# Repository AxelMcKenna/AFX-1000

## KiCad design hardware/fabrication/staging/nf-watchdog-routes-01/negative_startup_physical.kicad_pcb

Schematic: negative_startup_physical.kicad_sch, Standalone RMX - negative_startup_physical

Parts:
C1: 56nF50V C0G5% C1206C563J5GACTU - COMPLETE10% RECE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; PROPOSED_KEMET1206_LevelB
C2: 33nF50V C0G5% C1206C333J5GACTU - COMPLETE10% RECE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; PROPOSED_KEMET1206_LevelB
C3, C12, C39, C55, C56, C57, C58, C59, C60, C61, C62, C63, C64, C65, C66, C67, C68, C69, C70, C71, C72, C73, C74, C75, C76, C77, C78, C79, C80, C81, C82, C83, C84, C85, C86, C87, C88: 100nF 50V X7R10% C0603C104K5RACTU - bypass effect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; PROPOSED_KEMET0603_LevelB
C4, C31: 10uF 25V X7R MODULE INPUT FILTER/EFFECTIVE/INRUSH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; Capacitor_SMD__C_1206_3216Metric
C5, C32: 1uF 50V X7R MODULE OUTPUT FILTER/EFFECTIVE HOLD; Capacitor_SMD__C_1206_3216Metric
C6, C33: 1uF 25V X7R LTC4261 local VIN effective HOLD; Capacitor_SMD__C_1206_3216Metric
C7, C9, C11, C13, C34, C36, C38, C40: 100nF 25V C0G C1206C104J3GACTU; PROPOSED_KEMET1206_LevelB
C8, C10, C35, C37: 10nF 50V C0G COMPLETE10% TIMING RECEIVING; PROPOSED_KEMET1206_LevelB
C14, C15, C16, C17, C18, C19, C20, C21, C22, C23, C24, C25, C41, C42, C43, C44, C45, C46, C47, C48, C49: 100nF 50V C0G C1210C104J5GACTU - COMPLETE10% RAMP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; PROPOSED_KEMET1210_LevelB
C26, C27, C50, C51: 2.2uF 63V PET5% MKS2C042201K00JSSD - COMPLETE10% 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; Capacitor_THT__C_Rect_L7.2mm_W7.2mm_P5.00mm_FKS2_FKP2_MKS2_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
C28, C30, C52, C54: 47nF 50V C0G C1206C473J5GACTU; PROPOSED_KEMET1206_LevelB
C29, C53: 100nF 50V C0G C1210C104J5GACTU; PROPOSED_KEMET1210_LevelB
C89, C90, C91, C93, C94, C96: 100nF50V X7R10% C0603C104K5RACTU - EFFECTIVE/PDN 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; PROPOSED_KEMET0603_LevelB
C92, C95: 47nF50V C0G5% C1206C473J5GACTU - COMPLETE6% RECEI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; PROPOSED_KEMET1206_LevelB
C97, C98: 100nF25V C0G5% C1206C104J3GACTU - COMPLETE6% CT /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; PROPOSED_KEMET1206_LevelB
C99: 100nF25V C0G5% C1206C104J3GACTU - COMPLETE6% UVRE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; PROPOSED_KEMET1206_LevelB
C100: 100nF50V X7R10% C0603C104K5RACTU - LOCAL_BYPASS_E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; PROPOSED_KEMET0603_LevelB
J1: NEW NF03C CONTROL/KELVIN INTERFACE - physical con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; NC265_JST_PHD_B30B-PHDSS_2x15_P2.00mm_Vertical
J2: N19 NEW FORCE IN/OUT - connector and harness unse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; NC265_NC265_Force2_18AWG_P5_Drill2p2_Land3p8
J3: N19 E28 BANK GATE/COMMON CLAMP - physical interfa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; NC265_JST_PH_B2B-PH-K_1x02_P2.00mm_Vertical
J4: N12 NEW FORCE IN/OUT - connector and harness unse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; NC265_NC265_Force2_18AWG_P5_Drill2p2_Land3p8
J5: N12 E28 BANK GATE/COMMON CLAMP - physical interfa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; NC265_JST_PH_B2B-PH-K_1x02_P2.00mm_Vertical
J6: NEW MODULE INPUT ONLY - keyed JST XH2 receiving c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; NC265_JST_XH_B2B-XH-A_1x02_P2.50mm_Vertical
Q1, Q2: CSD19536KTT; Package_TO_SOT_SMD__TO-263-2
R1, R2, R8, R9: 10k; PROPOSED_TNPW0805_IPC28950
R3, R10: 205000ohm 0.1% TNPW0805205KBEEA - COMPLETE3% RECE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; PROPOSED_TNPW0805_IPC28950
R4, R11: 499ohm 0.1% TNPW0805499RBEEA - COMPLETE3% RECEIVI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; PROPOSED_TNPW0805_IPC28950
R5, R12, R95, R98, R99: 10000ohm 0.1% TNPW080510K0BEEA - COMPLETE3% RECEI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; PROPOSED_TNPW0805_IPC28950
R6, R7, R13, R14: 220ohm COMPLETE +/-3% RECEIVING; PROPOSED_TNPW0805_IPC28950
R15, R16, R17, R18, R19, R20, R21, R22: 47k 3% TOTAL RECEIVING; PROPOSED_TNPW0805_IPC28950
R23: 160000ohm COMPLETE0.1% RECEIVING; PROPOSED_TNPU0805_IPC28950
R24, R41, R63, R65, R80, R82: 10k COMPLETE0.1% RECEIVING; PROPOSED_TNPU0805_IPC28950
R25, R49: 8660ohm COMPLETE0.1% RECEIVING; PROPOSED_TNPU0805_IPC28950
R26, R50: 35.7ohm COMPLETE0.1% RECEIVING; PROPOSED_TNPU0603_IPC28950
R27, R31, R35, R44, R47, R51: 100k COMPLETE0.1% RECEIVING; PROPOSED_TNPU0805_IPC28950
R28, R32, R36, R37, R38, R39, R45, R48, R52, R53, R54, R55, R59, R76: 10k COMPLETE3% RECEIVING; PROPOSED_TNPW0805_IPC28950
R29, R46: 2000ohm COMPLETE0.1% RECEIVING; PROPOSED_TNPU0805_IPC28950
R30: 40.2ohm COMPLETE0.1% RECEIVING; PROPOSED_TNPU0603_IPC28950
R33: 6040ohm COMPLETE0.1% RECEIVING; PROPOSED_TNPU0805_IPC28950
R34: 75ohm COMPLETE0.1% RECEIVING; PROPOSED_TNPU0603_IPC28950
R40: 102000ohm COMPLETE0.1% RECEIVING; PROPOSED_TNPU0805_IPC28950
R42: 10700ohm COMPLETE0.1% RECEIVING; PROPOSED_TNPU0805_IPC28950
R43: 169ohm COMPLETE0.1% RECEIVING; PROPOSED_TNPU0805_IPC28950
R56, R57, R73, R74: 402ohm 1% CRCW2010402RFKEF - COMPLETE3% RECEIVING; PROPOSED_CRCW2010_reflow20035
R58, R60, R61, R66, R67, R68, R75, R77, R78, R83, R84, R85: 47k COMPLETE3% RECEIVING; PROPOSED_TNPW0805_IPC28950
R62, R79: 30.4k COMPLETE0.1% RECEIVING; PROPOSED_TNPU0805_IPC28950
R64, R81: 78.7k COMPLETE0.1% RECEIVING; PROPOSED_TNPU0805_IPC28950
R69: 0.33ohm COMPLETE5% SHUNT RECEIVING; PROPOSED_WSL2512_7m_to500m
R70, R87: 10ohm COMPLETE3% RECEIVING; PROPOSED_TNPW0805_IPC28950
R71, R88: 1M; PROPOSED_TNPW0805_IPC28950
R72: 27ohm COMPLETE3% RECEIVING; PROPOSED_TNPW0805_IPC28950
R86: 0.12ohm COMPLETE5% SHUNT RECEIVING; PROPOSED_WSL2512_7m_to500m
R89: 39ohm COMPLETE3% RECEIVING; PROPOSED_TNPW0805_IPC28950
R90, R91: 10k0.1% TNPW080510K0BEEA - COMPLETE3% RECEIVING; PROPOSED_TNPW0805_IPC28950
R92: 11300ohm 0.02% 2ppm TNPU080511K3HWEN00 - COMPLETE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; PROPOSED_TNPW0805_IPC28950
R93: 49.9ohm 0.1% TNPW080549R9BEEA - COMPLETE0.7% TRIM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; PROPOSED_TNPW0805_IPC28950
R94: 10000ohm 0.02% 2ppm TNPU080510K0HWEN00 - COMPLETE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; PROPOSED_TNPW0805_IPC28950
R96: 47000ohm 0.1% TNPW080547K0BEEA - COMPLETE3% RECEI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; PROPOSED_TNPW0805_IPC28950
R97: 680ohm 0.1% TNPW1206680RBEEA - COMPLETE3% RECEIVI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; PROPOSED_TNPW1206_IPC28950
U1, U2, U7, U8: SN74AUP1G74DCUR; NF05R_Manufacturer__TI_DCU0008A
U3, U9: TPS3431SDRBR; TI_DRB0008A_TPS3431
U4, U10: SN74LVC1G06DBVR; Package_TO_SOT_SMD__SOT-23-5
U5, U6, U11, U12: TLP4590AF(F; Package_DIP__DIP-6_W10.16mm
U13: OPA2333AID; Package_SO__SOIC-8_3.9x4.9mm_P1.27mm
U14: TLV1822DR; Package_SO__SOIC-8_3.9x4.9mm_P1.27mm
U15: TLV1824DR; Package_SO__SOIC-14_3.9x8.7mm_P1.27mm
U16, U27: SN74LVC2T45DCUR; NF05R_Manufacturer__TI_DCU0008A
U17, U22: TMR 1-1215; Converter_DCDC__Converter_DCDC_TRACO_TMR-1-xxxx_Single_THT
U18, U23: LTC4261IGN#PBF; Package_SO__SSOP-28_3.9x9.9mm_P0.635mm
U19, U24: ISO7721FDR; Package_SO__SOIC-8_3.9x4.9mm_P1.27mm
U20, U21, U25, U26, U52, U54, U56: TPS389001DSET; Package_SON__WSON-6_1.5x1.5mm_P0.5mm
U28, U30, U53, U55: SN74LVC1G17DCKR; NF05R_Manufacturer__TI_DCK0005A
U29, U31, U32, U33, U34, U49: SN74AUP2G14DCKR; NF05R_Manufacturer__TI_DCK0006A
U35, U36, U37, U38, U39, U40, U41, U42, U43, U44, U51: SN74HCS08PWR; Package_SO__TSSOP-14_4.4x5mm_P0.65mm
U45, U46: SN74HCS32PWR; Package_SO__TSSOP-14_4.4x5mm_P0.65mm
U47, U48: SN74HCS14PWR; Package_SO__TSSOP-14_4.4x5mm_P0.65mm
U50: SN74HCS02PWR; Package_SO__TSSOP-14_4.4x5mm_P0.65mm
U57: TPS22919DCKR; NF05R_Manufacturer__TI_DCK0006A
U58: SN74LVC1G14DCKR; NF05R_Manufacturer__TI_DCK0005A

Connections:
/ABS_AUX_CT: C99.1, U56.5 (CT)
/ABS_AUX_FAULT: J1.7 (ABS_AUX_FAULT_MONITOR_OUTPUT_ONLY), R17.1, U48.13 (6A), U58.4 (Y)
/ABS_AUX_READY: U48.12 (6Y), U51.13 (4B)
/ABS_AUX_SENSE: R93.2, R94.1, U56.1 (SENSE)
/ABS_AUX_TOP_TRIM: R92.2, R93.1
/AGND: C1.2, C2.2, C3.2, C12.2, C39.2, C55.2, C56.2, C57.2, C58.2, C59.2, C60.2, C61.2, C62.2, C63.2, C64.2, C65.2, C66.2, C67.2, C68.2, C69.2, C70.2, C71.2, C72.2, C73.2, C74.2, C75.2, C76.2, C77.2, C78.2, C79.2, C80.2, C81.2, C82.2, C83.2, C84.2, C85.2, C86.2, C87.2, C88.2, C89.2, C90.2, C91.2, C92.2, C93.2, C94.2, C95.2, C96.2, C97.2, C98.2, C99.2, C100.2, J1.2 (AGND), R3.2, R10.2, R15.2, R16.2, R17.2, R18.2, R19.2, R20.2, R21.2, R22.2, R27.2, R31.2, R35.2, R44.2, R47.2, R51.2, R59.2, R61.2, R67.2, R68.2, R76.2, R78.2, R84.2, R85.2, R94.2, R96.2, R97.2, U1.4 (GND), U2.4 (GND), U3.4 (GND), U3.9 (EP), U4.3 (GND), U7.4 (GND), U8.4 (GND), U9.4 (GND), U9.9 (EP), U10.3 (GND), U13.3 (INA+), U13.4 (V-), U13.5 (INB+), U14.4 (V-), U15.12 (V-), U16.4 (GND), U19.5 (GND2), U24.5 (GND2), U27.4 (GND), U28.3 (GND), U29.2 (GND), U30.3 (GND), U31.2 (GND), U32.2 (GND), U33.2 (GND), U34.2 (GND), U35.7 (GND), U36.7 (GND), U37.7 (GND), U38.7 (GND), U39.7 (GND), U40.7 (GND), U41.7 (GND), U42.7 (GND), U43.7 (GND), U44.7 (GND), U45.7 (GND), U46.7 (GND), U46.12 (4A), U46.13 (4B), U47.7 (GND), U48.7 (GND), U49.2 (GND), U50.7 (GND), U51.7 (GND), U52.2 (GND), U53.3 (GND), U54.2 (GND), U55.3 (GND), U56.2 (GND), U57.2 (GND), U58.3 (GND)
/AUX2V6: C3.1, C12.1, C56.1, C57.1, C58.1, C59.1, C60.1, C61.1, C62.1, C63.1, C64.1, C65.1, C66.1, C67.1, C68.1, C69.1, C70.1, C71.1, C72.1, C73.1, C74.1, C75.1, C76.1, C77.1, C78.1, C79.1, C80.1, C81.1, C82.1, C83.1, C84.1, C85.1, C86.1, C87.1, C88.1, C89.1, C90.1, C91.1, C93.1, C94.1, C96.1, C100.1, J1.1 (AUX2V6), R1.1, R2.1, R8.1, R9.1, R37.1, R38.1, R39.1, R53.1, R54.1, R55.1, R90.1, R91.1, R92.1, U1.7 (PRE_N), U1.8 (VCC), U2.2 (D), U2.7 (PRE_N), U2.8 (VCC), U3.1 (VDD), U4.5 (VCC), U7.7 (PRE_N), U7.8 (VCC), U8.2 (D), U8.7 (PRE_N), U8.8 (VCC), U9.1 (VDD), U10.5 (VCC), U13.8 (V+), U14.8 (V+), U15.3 (V+), U16.1 (VCCA), U16.5 (DIR), U27.8 (VCCB), U28.5 (VCC), U29.5 (VCC), U30.5 (VCC), U31.5 (VCC), U32.5 (VCC), U33.5 (VCC), U34.5 (VCC), U35.14 (VCC), U36.14 (VCC), U37.14 (VCC), U38.14 (VCC), U39.14 (VCC), U40.14 (VCC), U41.14 (VCC), U42.14 (VCC), U43.14 (VCC), U44.14 (VCC), U45.14 (VCC), U46.14 (VCC), U47.14 (VCC), U48.14 (VCC), U49.5 (VCC), U50.14 (VCC), U51.14 (VCC), U52.3 (MR), U52.4 (VDD), U53.5 (VCC), U54.3 (MR), U54.4 (VDD), U55.5 (VCC), U58.5 (VCC)
/AUX_VALID: J1.5 (AUX_VALID), R16.1, U35.1 (1A)
/CLAMP_LED_SUPPLY: C98.1, R4.1, R11.1, R97.1, U57.6 (VOUT)
/CLAMP_SUPPLY_ENABLE: R95.2, R96.1, U56.6 (RESET_N), U57.3 (ON), U58.2 (A)
/DIG5_FORCE: C39.1, C55.1, C97.1, J1.3 (DIG5_FORCE), R95.1, U16.8 (VCCB), U19.8 (VCC2), U24.8 (VCC2), U27.1 (VCCA), U27.5 (DIR), U56.3 (MR), U56.4 (VDD), U57.1 (IN)
/E28_COMBINED_FAULT_REQUEST: J1.14 (E28_COMBINED_FAULT_REQUEST), U34.4 (2Y)
/E28_COMBINED_FAULT_REQUEST_BUFFER_MID: U34.3 (2A), U34.6 (1Y)
/E28_COMBINED_FAULT_REQUEST_HCS: U34.1 (1A), U46.6 (2Y)
/E28_NATIVE_FAULT_REQUEST: J1.13 (E28_NATIVE_FAULT_REQUEST), U46.4 (2A)
/E28_NOT_FAULT: J1.15 (E28_NOT_FAULT), R22.1, U44.4 (2A)
/GLOBAL_MASTER: J1.6 (GLOBAL_MASTER), R15.1, U35.2 (1B)
/GLOBAL_VALID: U35.3 (1Y), U35.4 (2A), U35.5 (2B), U35.12 (4A), U37.4 (2A), U38.5 (2B), U38.13 (4B), U40.12 (4A), U41.13 (4B), U48.11 (5A), U51.1 (1A), U51.4 (2A)
/GUARDED_12V_FORCE: C4.1, C31.1, J6.1 (GUARDED12), U17.2 (+VIN), U22.2 (+VIN)
/MODULE_INPUT_GND: C4.2, C31.2, J6.2 (MODULE_RETURN), U17.1 (-VIN), U22.1 (-VIN)
/N12_ARM_CONDITIONED: J1.24 (N12_ARM_MONITOR_OUTPUT_ONLY), R20.1, U30.4 (Y), U39.1 (1A), U40.13 (4B), U41.12 (4A), U54.1 (SENSE)
/N12_ARM_Q: U30.2 (A), U50.10 (3Y), U50.12 (4B)
/N12_ARM_QBAR: U50.9 (3B), U50.13 (4Y)
/N12_ARM_SET: U50.11 (4A), U51.8 (3Y)
/N12_BANK_CLAMP_GATE: R14.2, U12.4 (D1)
/N12_BANK_COMMON: J5.2 (BANK_COMMON), U12.6 (D2)
/N12_BANK_GATE: J5.1 (BANK_GATE), R14.1
/N12_BIAS_CT: C37.1, U25.5 (CT)
/N12_BIAS_HOST5: R84.1, U24.6 (OUTB), U27.3 (A2)
/N12_BIAS_RESET_N: R83.2, U24.3 (INB), U25.6 (RESET_N), U26.6 (RESET_N)
/N12_BIAS_SENSE: R79.2, R80.1, U25.1 (SENSE)
/N12_BIAS_VALID: J1.17 (N12_BIAS_VALID), R85.1, U27.6 (B2), U43.13 (4B)
/N12_CG_SERIES: C52.1, R87.2
/N12_CLAMPS_RELEASE: J1.28 (N12_CLAMPS_RELEASE), R10.1, U10.2 (A), U33.4 (2Y)
/N12_CLAMPS_RELEASE_BUFFER_MID: U33.3 (2A), U33.6 (1Y)
/N12_CLAMPS_RELEASE_HCS: U33.1 (1A), U42.3 (1Y)
/N12_CLAMP_LED_A: R11.2, R12.1, U11.1 (LED_A)
/N12_CLAMP_LED_K: R99.2, U10.4 (Y), U12.2 (LED_K)
/N12_CLAMP_LED_MID: R12.2, R99.1, U11.2 (LED_K), U12.1 (LED_A)
/N12_COMPLETE: J1.27 (N12_COMPLETE), U8.5 (Q), U39.12 (4A), U44.12 (4A)
/N12_COMPLETE_CLK: U8.1 (CLK), U41.8 (3Y)
/N12_COMPLETE_CLR_N: U8.6 (CLR_N), U41.11 (4Y)
/N12_CONTROLLER_ON: R77.1, U23.2 (ON), U24.2 (OUTA)
/N12_CR_TOP: C41.1, C42.1, C43.1, C44.1, C45.1, C46.1, C47.1, C48.1, C49.1, R89.2
/N12_CWD: C2.1, U9.2 (CWD)
/N12_DRAIN_SENSE: R88.2, U23.16 (DRAIN)
/N12_E28_SRC: C41.2, C42.2, C43.2, C44.2, C45.2, C46.2, C47.2, C48.2, C49.2, J4.2 (E28_SRC), Q2.2 (D), R88.1
/N12_F0: U45.8 (3Y), U45.12 (4A)
/N12_FAULT_REQUEST: J1.26 (N12_FAULT_REQUEST), U45.11 (4Y), U46.2 (1B)
/N12_FEED_MID: R73.2, R74.1
/N12_F_OUTPUT: U39.11 (4Y), U45.13 (4B)
/N12_F_SOURCE: U39.3 (1Y), U45.9 (3A)
/N12_F_TIMEOUT: U39.8 (3Y), U45.10 (3B)
/N12_F_WD_ARM: U39.6 (2Y), U39.9 (3A)
/N12_INTVCC: C34.1, C36.1, C38.1, C40.1, R79.1, R83.1, U23.5 (SDAI), U23.6 (SCL), U23.7 (INTVCC), U23.8 (UVL), U23.9 (UVH), U23.22 (FLTIN), U24.1 (VCC1), U25.3 (MR_N), U25.4 (VDD), U26.3 (MR_N), U26.4 (VDD)
/N12_ISO24: C32.1, R73.1, U22.4 (+VOUT)
/N12_NOT_COMPLETE: U8.3 (NOT_Q), U9.5 (SET1)
/N12_NOT_PERMIT: U7.3 (NOT_Q), U9.6 (WDI)
/N12_NOT_READY: U39.13 (4B), U47.10 (5Y)
/N12_NOT_SAFE: U39.2 (1B), U47.8 (4Y)
/N12_NOT_WDO: U39.10 (3B), U47.12 (6Y)
/N12_OUTPUT_OV_GOOD: R55.2, U15.13 (OUT4), U43.10 (3B), U44.2 (1B)
/N12_OUTPUT_QUALIFIED: U44.11 (4Y), U48.5 (3A)
/N12_OUTPUT_UV_GOOD: R54.2, U15.14 (OUT3), U44.1 (1A)
/N12_OUT_INV: R41.1, R45.1, R48.1, U13.7 (OUTB)
/N12_OUT_OV_REF: R46.2, R47.1, U15.11 (IN4+)
/N12_OUT_OV_SENSE: R48.2, U15.10 (IN4-)
/N12_OUT_SUM: R40.2, R41.2, U13.6 (INB-)
/N12_OUT_UV_REF: R43.2, R44.1, U15.8 (IN3-)
/N12_OUT_UV_RMID: R42.2, R43.1
/N12_OUT_UV_SENSE: R45.2, U15.9 (IN3+)
/N12_OV_OK: J1.10 (N12_OV_OK), U43.5 (2B)
/N12_OV_SENSE: J1.12 (N12_OV_SENSE), R52.1
/N12_P03_SRC: C32.2, C33.2, C34.2, C35.2, C36.2, C37.2, C38.2, C40.2, C50.2, C51.2, C52.2, C53.2, C54.2, J4.1 (P03_SRC), R75.2, R76.1, R77.2, R80.2, R82.2, R86.1, U22.6 (-VOUT), U23.1 (PGI), U23.3 (ALERT), U23.10 (ADIN2), U23.11 (OV), U23.13 (VEE), U23.23 (ADIN), U23.24 (ADR0), U23.25 (ADR1), U23.26 (EN), U23.27 (PG), U24.4 (GND1), U25.2 (GND), U26.2 (GND)
/N12_PASS_CLAMP_GATE: R13.2, U11.4 (D1)
/N12_PASS_GATE: Q2.1 (G), R13.1, R87.1, U23.15 (GATE)
/N12_PASS_SOURCE: Q2.3 (S), R86.2, U11.6 (D2), U23.14 (SENSE)
/N12_PCLR0: U40.11 (4Y), U41.1 (1A), U42.1 (1A)
/N12_PCLR1: U41.3 (1Y), U41.4 (2A)
/N12_PERMIT: U7.5 (Q), U16.3 (A2), U41.9 (3A)
/N12_PERMIT_CLR_N: U7.6 (CLR_N), U41.6 (2Y)
/N12_PERMIT_D: U7.2 (D), U40.8 (3Y), U51.10 (3B)
/N12_PROTECTED: J1.29 (N12_PROTECTED), R40.1
/N12_RAMP: C50.1, C51.1, R89.1, U23.18 (RAMP)
/N12_READY: U41.10 (3B), U44.3 (1Y), U44.13 (4B), U47.11 (5A)
/N12_RUN_HOST5: R78.1, U16.6 (B2), U24.7 (INA)
/N12_SAFE: U40.5 (2B), U41.5 (2B), U43.11 (4Y), U47.9 (4A)
/N12_SOURCE_SAFE0: U43.6 (2Y), U43.9 (3A)
/N12_SOURCE_SAFE1: U43.8 (3Y), U43.12 (4A)
/N12_SOURCE_UV_GOOD: R53.2, U14.7 (OUT2), U43.4 (2A)
/N12_SOURCE_UV_REF: R50.2, R51.1, U14.6 (IN2-)
/N12_SOURCE_UV_RMID: R49.2, R50.1
/N12_SOURCE_UV_SENSE: R52.2, U14.5 (IN2+)
/N12_SS: C53.1, U23.19 (SS)
/N12_STAGE_ENABLED: U38.12 (4A), U39.4 (2A), U51.6 (2Y), U51.9 (3A)
/N12_START: J1.25 (N12_START_MONITOR_OUTPUT_ONLY), R21.1, U31.1 (1A), U55.4 (Y)
/N12_START_ARMED: U40.3 (1Y), U40.4 (2A)
/N12_START_CONDITIONED: U7.1 (CLK), U31.4 (2Y)
/N12_START_CONDITIONED_BUFFER_MID: U31.3 (2A), U31.6 (1Y)
/N12_START_CT: C95.1, U54.5 (CT)
/N12_START_DELAY_N: R91.2, U54.6 (RESET_N), U55.2 (A)
/N12_START_SAFE: U40.6 (2Y), U40.9 (3A)
/N12_TMR: C54.1, U23.20 (TMR)
/N12_VIN: C33.1, R74.2, R75.1, R81.1, U23.21 (VIN)
/N12_VIN_VALID_CT: C35.1, U26.5 (CT)
/N12_VIN_VALID_SENSE: R81.2, R82.1, U26.1 (SENSE)
/N12_WDO: R8.2, U9.7 (WDO), U40.2 (1B), U47.13 (6A)
/N12_WD_ARMED: R9.2, U9.8 (ENOUT), U39.5 (2B), U40.1 (1A)
/N12_WD_ENABLE: U9.3 (EN), U38.11 (4Y)
/N19_ARM_CONDITIONED: J1.18 (N19_ARM_MONITOR_OUTPUT_ONLY), R18.1, U28.4 (Y), U35.9 (3A), U37.5 (2B), U38.4 (2A), U52.1 (SENSE)
/N19_ARM_Q: U28.2 (A), U50.1 (1Y), U50.6 (2B)
/N19_ARM_QBAR: U50.3 (1B), U50.4 (2Y)
/N19_ARM_SET: U50.5 (2A), U51.3 (1Y)
/N19_BANK_CLAMP_GATE: R7.2, U6.4 (D1)
/N19_BANK_COMMON: J3.2 (BANK_COMMON), U6.6 (D2)
/N19_BANK_GATE: J3.1 (BANK_GATE), R7.1
/N19_BIAS_CT: C10.1, U20.5 (CT)
/N19_BIAS_HOST5: R67.1, U19.6 (OUTB), U27.2 (A1)
/N19_BIAS_RESET_N: R66.2, U19.3 (INB), U20.6 (RESET_N), U21.6 (RESET_N)
/N19_BIAS_SENSE: R62.2, R63.1, U20.1 (SENSE)
/N19_BIAS_VALID: J1.16 (N19_BIAS_VALID), R68.1, U27.7 (B1), U42.13 (4B)
/N19_CG_SERIES: C28.1, R70.2
/N19_CLAMPS_RELEASE: J1.22 (N19_CLAMPS_RELEASE), R3.1, U4.2 (A), U32.4 (2Y)
/N19_CLAMPS_RELEASE_BUFFER_MID: U32.3 (2A), U32.6 (1Y)
/N19_CLAMPS_RELEASE_HCS: U32.1 (1A), U38.8 (3Y)
/N19_CLAMP_LED_A: R4.2, R5.1, U5.1 (LED_A)
/N19_CLAMP_LED_K: R98.2, U4.4 (Y), U6.2 (LED_K)
/N19_CLAMP_LED_MID: R5.2, R98.1, U5.2 (LED_K), U6.1 (LED_A)
/N19_COMPLETE: J1.21 (N19_COMPLETE), U2.5 (Q), U36.4 (2A), U44.9 (3A)
/N19_COMPLETE_CLK: U2.1 (CLK), U38.3 (1Y)
/N19_COMPLETE_CLR_N: U2.6 (CLR_N), U38.6 (2Y)
/N19_CONTROLLER_ON: R60.1, U18.2 (ON), U19.2 (OUTA)
/N19_CR_TOP: C14.1, C15.1, C16.1, C17.1, C18.1, C19.1, C20.1, C21.1, C22.1, C23.1, C24.1, C25.1, R72.2
/N19_CWD: C1.1, U3.2 (CWD)
/N19_DRAIN_SENSE: R71.2, U18.16 (DRAIN)
/N19_E28_SRC: C14.2, C15.2, C16.2, C17.2, C18.2, C19.2, C20.2, C21.2, C22.2, C23.2, C24.2, C25.2, J2.2 (E28_SRC), Q1.2 (D), R71.1
/N19_F0: U45.3 (1Y), U45.4 (2A)
/N19_FAULT_REQUEST: J1.20 (N19_FAULT_REQUEST), U45.6 (2Y), U46.1 (1A)
/N19_FEED_MID: R56.2, R57.1
/N19_F_OUTPUT: U36.6 (2Y), U45.5 (2B)
/N19_F_SOURCE: U35.8 (3Y), U45.1 (1A)
/N19_F_TIMEOUT: U36.3 (1Y), U45.2 (1B)
/N19_F_WD_ARM: U35.11 (4Y), U36.1 (1A)
/N19_INTVCC: C7.1, C9.1, C11.1, C13.1, R62.1, R66.1, U18.5 (SDAI), U18.6 (SCL), U18.7 (INTVCC), U18.8 (UVL), U18.9 (UVH), U18.22 (FLTIN), U19.1 (VCC1), U20.3 (MR_N), U20.4 (VDD), U21.3 (MR_N), U21.4 (VDD)
/N19_ISO24: C5.1, R56.1, U17.4 (+VOUT)
/N19_NOT_COMPLETE: U2.3 (NOT_Q), U3.5 (SET1)
/N19_NOT_PERMIT: U1.3 (NOT_Q), U3.6 (WDI)
/N19_NOT_READY: U36.5 (2B), U47.4 (2Y)
/N19_NOT_SAFE: U35.10 (3B), U47.2 (1Y)
/N19_NOT_WDO: U36.2 (1B), U47.6 (3Y)
/N19_OUTPUT_OV_GOOD: R39.2, U15.1 (OUT2), U42.10 (3B), U43.2 (1B)
/N19_OUTPUT_QUALIFIED: U44.8 (3Y), U48.3 (2A), U51.5 (2B)
/N19_OUTPUT_UV_GOOD: R38.2, U15.2 (OUT1), U43.1 (1A)
/N19_OUT_INV: R24.1, R28.1, R32.1, U13.1 (OUTA)
/N19_OUT_OV_REF: R30.2, R31.1, U15.7 (IN2+)
/N19_OUT_OV_RMID: R29.2, R30.1
/N19_OUT_OV_SENSE: R32.2, U15.6 (IN2-)
/N19_OUT_SUM: R23.2, R24.2, U13.2 (INA-)
/N19_OUT_UV_REF: R26.2, R27.1, U15.4 (IN1-)
/N19_OUT_UV_RMID: R25.2, R26.1
/N19_OUT_UV_SENSE: R28.2, U15.5 (IN1+)
/N19_OV_OK: J1.9 (N19_OV_OK), U42.5 (2B)
/N19_OV_SENSE: J1.11 (N19_OV_SENSE), R36.1
/N19_P03_SRC: C5.2, C6.2, C7.2, C8.2, C9.2, C10.2, C11.2, C13.2, C26.2, C27.2, C28.2, C29.2, C30.2, J2.1 (P03_SRC), R58.2, R59.1, R60.2, R63.2, R65.2, R69.1, U17.6 (-VOUT), U18.1 (PGI), U18.3 (ALERT), U18.10 (ADIN2), U18.11 (OV), U18.13 (VEE), U18.23 (ADIN), U18.24 (ADR0), U18.25 (ADR1), U18.26 (EN), U18.27 (PG), U19.4 (GND1), U20.2 (GND), U21.2 (GND)
/N19_PASS_CLAMP_GATE: R6.2, U5.4 (D1)
/N19_PASS_GATE: Q1.1 (G), R6.1, R70.1, U18.15 (GATE)
/N19_PASS_SOURCE: Q1.3 (S), R69.2, U5.6 (D2), U18.14 (SENSE)
/N19_PCLR0: U37.6 (2Y), U37.9 (3A), U38.9 (3A)
/N19_PCLR1: U37.8 (3Y), U37.12 (4A)
/N19_PERMIT: U1.5 (Q), U16.2 (A1), U38.1 (1A)
/N19_PERMIT_CLR_N: U1.6 (CLR_N), U37.11 (4Y)
/N19_PERMIT_D: U1.2 (D), U37.3 (1Y), U51.2 (1B)
/N19_PROTECTED: J1.23 (N19_PROTECTED), R23.1
/N19_RAMP: C26.1, C27.1, R72.1, U18.18 (RAMP)
/N19_READY: U38.2 (1B), U43.3 (1Y), U44.10 (3B), U47.3 (2A)
/N19_RUN_HOST5: R61.1, U16.7 (B1), U19.7 (INA)
/N19_SAFE: U36.13 (4B), U37.13 (4B), U47.1 (1A), U51.11 (4Y)
/N19_SAFE_SOURCE: U42.11 (4Y), U51.12 (4A)
/N19_SOURCE_SAFE0: U42.6 (2Y), U42.9 (3A)
/N19_SOURCE_SAFE1: U42.8 (3Y), U42.12 (4A)
/N19_SOURCE_UV_GOOD: R37.2, U14.1 (OUT1), U42.4 (2A)
/N19_SOURCE_UV_REF: R34.2, R35.1, U14.2 (IN1-)
/N19_SOURCE_UV_RMID: R33.2, R34.1
/N19_SOURCE_UV_SENSE: R36.2, U14.3 (IN1+)
/N19_SS: C29.1, U18.19 (SS)
/N19_START: J1.19 (N19_START_MONITOR_OUTPUT_ONLY), R19.1, U29.1 (1A), U53.4 (Y)
/N19_START_ARMED: U36.8 (3Y), U36.12 (4A)
/N19_START_CONDITIONED: U1.1 (CLK), U29.4 (2Y)
/N19_START_CONDITIONED_BUFFER_MID: U29.3 (2A), U29.6 (1Y)
/N19_START_CT: C92.1, U52.5 (CT)
/N19_START_DELAY_N: R90.2, U52.6 (RESET_N), U53.2 (A)
/N19_START_SAFE: U36.11 (4Y), U37.1 (1A)
/N19_TMR: C30.1, U18.20 (TMR)
/N19_VIN: C6.1, R57.2, R58.1, R64.1, U18.21 (VIN)
/N19_VIN_VALID_CT: C8.1, U21.5 (CT)
/N19_VIN_VALID_SENSE: R64.2, R65.1, U21.1 (SENSE)
/N19_WDO: R1.2, U3.7 (WDO), U36.10 (3B), U47.5 (3A)
/N19_WD_ARMED: R2.2, U3.8 (ENOUT), U35.13 (4B), U36.9 (3A)
/N19_WD_ENABLE: U3.3 (EN), U35.6 (2Y)
/NF_FAULT_REQUEST: U46.3 (1Y), U46.5 (2B), U48.1 (1A)
/NF_NOT_OUTPUT_VALID: U46.8 (3Y), U48.9 (4A)
/NF_NO_FAULT: U37.2 (1B), U37.10 (3B), U38.10 (3B), U40.10 (3B), U41.2 (1B), U42.2 (1B), U44.6 (2Y)
/NF_OUTPUT_VALID: J1.30 (NF_OUTPUT_VALID), U49.4 (2Y)
/NF_OUTPUT_VALID_BUFFER_MID: U49.3 (2A), U49.6 (1Y)
/NF_OUTPUT_VALID_HCS: U48.8 (4Y), U49.1 (1A)
/NOT_GLOBAL_VALID: U48.10 (5Y), U50.2 (1A), U50.8 (3A)
/NOT_N12_OUTPUT_QUALIFIED: U46.10 (3B), U48.6 (3Y)
/NOT_N19_OUTPUT_QUALIFIED: U46.9 (3A), U48.4 (2Y)
/NOT_NF_FAULT_REQUEST: U44.5 (2B), U48.2 (1Y)
/PROTECT_REF: J1.8 (PROTECT_REF), R25.1, R29.1, R33.1, R42.1, R46.1, R49.1

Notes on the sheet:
NF06P: captured265-part NF05R circuit with explicit physical-land/connector proposals.
Actual primitive/MPN heights, complete tolerances, routing, return coupling and installed assembly require fresh review.
Prototype only; physical/partial-power/faultenergy/fabrication acceptance FALSE.

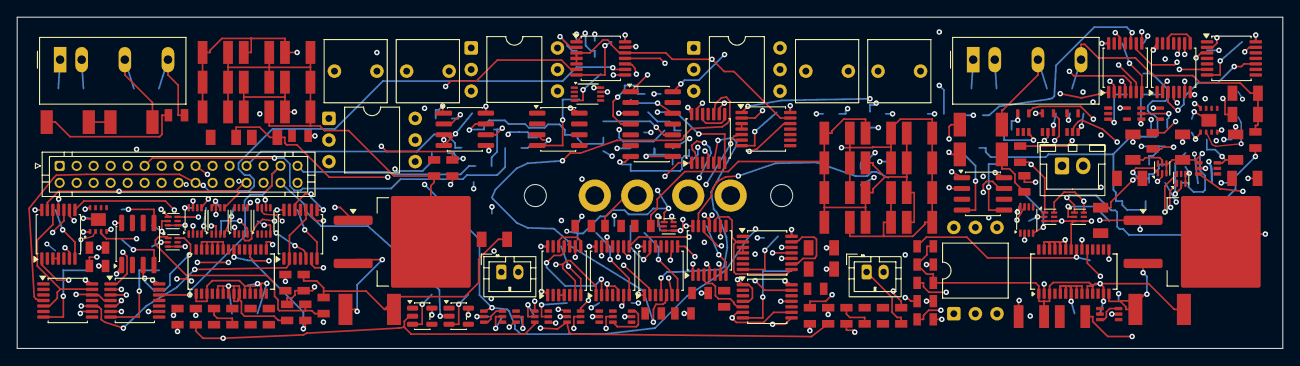
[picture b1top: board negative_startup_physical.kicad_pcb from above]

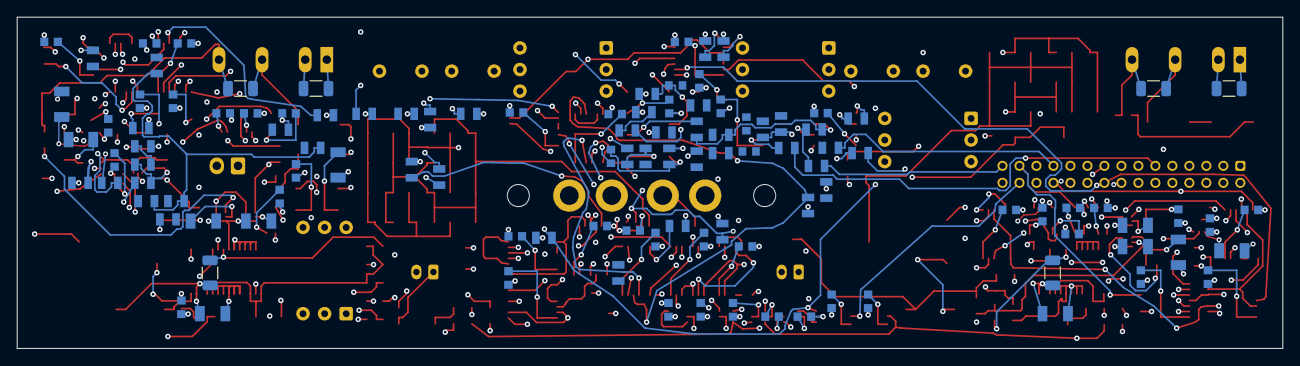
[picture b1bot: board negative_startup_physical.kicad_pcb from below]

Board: 6 copper layers, 149.0 x 39.0 mm, 267 parts (113 on the bottom side), 210 nets.

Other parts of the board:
H101, H102: STRAIN_POST_2p6_NPTH_RECEIVING

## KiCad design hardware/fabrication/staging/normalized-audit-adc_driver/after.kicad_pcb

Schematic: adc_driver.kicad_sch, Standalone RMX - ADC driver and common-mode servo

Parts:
C1, C2, C15, C16: 1pF C0G +/-0.1pF; C_0402_1005Metric
C3, C17: 47pF C0G 5%; C_0805_2012Metric
C4, C5, C18, C19: 22pF C0G 5%; C_0805_2012Metric
C6, C20: 100nF 25V X7R; C_0805_2012Metric
C7, C21: 1uF 63V film 10%; C_Rect_L7.2mm_W5.0mm_P5.00mm
C8, C22: 10uF 16V X7R; C_1206_3216Metric
C9, C23: 47uF 25V X7S; C_1210_3225Metric
C10, C11, C24, C25: 47uF 6.3V X7S; C_1206_3216Metric
C12, C26: 2.2uF 16V X7R; C_0805_2012Metric
C13, C14, C27, C28: 100nF 16V X7R; C_0402_1005Metric
C29, C30, C31, C32: 100nF 50V X7R; C_0805_2012Metric
C33, C34: 10uF 50V X7R; C_1206_3216Metric
C35, C36: 100nF 16V X7R; C_0603_1608Metric
D1, D2: BAT54S,215; SOT-23
J1: Conn_01x03; PinHeader_1x03_P2.54mm_Vertical
J2: Conn_02x10_Odd_Even; PinHeader_2x10_P2.54mm_Vertical
J3, J4: Conn_01x04; PinHeader_1x04_P2.54mm_Vertical
R1, R2, R17, R18: 2.49k 0.05%; R_0402_1005Metric
R3, R4, R19, R20: 1.21k 0.05%; R_0402_1005Metric
R5, R6, R21, R22: 3.3R 1%; R_0805_2012Metric
R7, R23: 1M 1%; R_0805_2012Metric
R8, R9, R24, R25: 100k 0.01%; R_0805_2012Metric
R10, R11, R26, R27: 10k 0.1%; R_0805_2012Metric
R12, R28: 10M 1%; R_0805_2012Metric
R13, R29: 10k 1%; R_0805_2012Metric
R14, R30: 47k 1%; R_0805_2012Metric
R15, R31: 68k 1%; R_0805_2012Metric
R16, R32: 0.1R 1%; R_0805_2012Metric
R33: 1k 1%; R_0805_2012Metric
R34, R36: 100k 0.01%; R_0603_1608Metric
R35, R37, R39, R41: 10k 0.01%; R_0603_1608Metric
R38: 161k 0.01%; R_0805_2012Metric
R40: 240k 0.01%; R_0805_2012Metric
R42, R43: 10k 1%; R_0603_1608Metric
R44: 100k 1%; R_0603_1608Metric
U1, U2: THS4551IDGKR; VSSOP-8_3x3mm_P0.65mm
U3: OPA1656ID; SOIC-8_3.9x4.9mm_P1.27mm
U4: OPA4192ID; SOIC-14_3.9x8.7mm_P1.27mm
U5, U6: LM7705MM/NOPB; VSSOP-8_3x3mm_P0.65mm
U7: TLV9024DR; SOIC-14_3.9x8.7mm_P1.27mm
U8: TPS3808G50DBVR; SOT-23-6

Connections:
/ADC_LN: C3.2, C5.1, J2.4, R6.2
/ADC_LP: C3.1, C4.1, J2.1, R5.2
/ADC_RN: C17.2, C19.1, J2.12, R22.2
/ADC_RP: C17.1, C18.1, J2.9, R21.2
/AGND: C4.2, C5.2, C6.2, C9.2, C10.2, C11.2, C12.2, C13.2, C14.2, C18.2, C19.2, C20.2, C23.2, C24.2, C25.2, C26.2, C27.2, C28.2, C29.2, C30.2, C31.2, C32.2, C33.2, C34.2, C35.2, C36.2, D1.1 (A1), D2.1 (A1), J1.2, J2.3, J2.6, J2.8, J2.11, J2.14, J2.16, J2.20, J3.2, J4.1, R2.1, R7.2, R9.2, R18.1, R23.2, R25.2, R33.2, R39.2, R41.2, R44.2, U5.2 (VSS_A), U5.3 (SD), U5.5 (VSS_B), U6.2 (VSS_A), U6.3 (SD), U6.5 (VSS_B), U7.12, U8.2
/BIAS_OK: J2.18, R42.2, U7.1, U7.2, U7.13, U7.14, U8.3
/BIAS_SHIFT_L: R34.2, R35.1, U7.4, U7.7
/BIAS_SHIFT_R: R36.2, R37.1, U7.8, U7.11
/BUF_L: R1.1, U3.1 (A_OUT), U3.2 (A-)
/BUF_R: R17.1, U3.6 (B-), U3.7 (B_OUT)
/CM_DRIVE_L: C7.1, R12.1, R13.1, U4.7 (B_OUT)
/CM_DRIVE_R: C21.1, R28.1, R29.1, U4.14 (D_OUT)
/CM_SENSE_L: C7.2, R10.2, R11.2, R12.2, U4.6 (B-)
/CM_SENSE_R: C21.2, R26.2, R27.2, R28.2, U4.13 (D-)
/DRV_ENABLE: J2.19, J4.2, R43.1
/DRV_LN: C1.1, R6.1, U1.5 (OUT-)
/DRV_LP: C2.1, R5.1, U1.4 (OUT+)
/DRV_RN: C15.1, R22.1, U2.5 (OUT-)
/DRV_RP: C16.1, R21.1, U2.4 (OUT+)
/FB_N_L: C2.2, R2.2, R4.2, U1.1 (IN-)
/FB_N_R: C16.2, R18.2, R20.2, U2.1 (IN-)
/FB_P_L: C1.2, R1.2, R3.2, U1.8 (IN+)
/FB_P_R: C15.2, R17.2, R19.2, U2.8 (IN+)
/FLY_N_L: C8.2, U5.8 (CF-)
/FLY_N_R: C22.2, U6.8 (CF-)
/FLY_P_L: C8.1, U5.1 (CF+)
/FLY_P_R: C22.1, U6.1 (CF+)
/N12: C30.1, C32.1, C34.1, J3.3, U3.4 (V-), U4.11 (V-)
/NBIAS_L: C11.1, C14.1, J4.3, R15.2, R16.2, R35.2, U1.6 (VS-)
/NBIAS_R: C25.1, C28.1, J4.4, R31.2, R32.2, R37.2, U2.6 (VS-)
/NPUMP_L: C10.1, R16.1, U5.6 (VOUT)
/NPUMP_R: C24.1, R32.1, U6.6 (VOUT)
/P12: C29.1, C31.1, C33.1, J3.1, U3.8 (V+), U4.4 (V+)
/PD_GATED: J2.17, R14.1, R30.1, R43.2, R44.1, U8.1
/PD_L: R14.2, R15.1, U1.7 (PD)
/PD_R: R30.2, R31.1, U2.7 (PD)
/PRE_OUT_L: J1.1, R7.1, U3.3 (A+)
/PRE_OUT_R: J1.3, R23.1, U3.5 (B+)
/REF_ADC1: J2.7, R8.1
/REF_ADC2: J2.15, R24.1
/REF_DIV_L: C6.1, R8.2, R9.1, U4.3 (A+)
/REF_DIV_R: C20.1, R24.2, R25.1, U4.10 (C+)
/REF_HALF_L: U4.1 (A_OUT), U4.2 (A-), U4.5 (B+)
/REF_HALF_R: U4.8 (C_OUT), U4.9 (C-), U4.12 (D+)
/RES_L: C9.1, U5.7 (CRES)
/RES_R: C23.1, U6.7 (CRES)
/SENSE_LN: J2.5, R3.1, R11.1
/SENSE_LP: J2.2, R4.1, R10.1
/SENSE_RN: J2.13, R19.1, R27.1
/SENSE_RP: J2.10, R20.1, R26.1
/THRESH_LOWER: R40.2, R41.1, U7.6, U7.10
/THRESH_UPPER: R38.2, R39.1, U7.5, U7.9
/V5_REG: C12.1, C13.1, C26.1, C27.1, C35.1, C36.1, D1.2 (K2), D2.2 (K2), J3.4, R33.1, R34.1, R36.1, R38.1, R40.1, R42.1, U1.3 (VS+), U2.3 (VS+), U5.4 (VDD), U6.4 (VDD), U7.3, U8.5, U8.6
/VOCM_L: D1.3 (K1_A2), R13.2, U1.2 (VOCM)
/VOCM_R: D2.3 (K1_A2), R29.2, U2.2 (VOCM)

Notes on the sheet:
E12-R2 design-repair candidate; no fabrication or physical qualification
Separate force/sense interface; final ESS pin integration and parasitic model required
Both bias windows and V5 supervisor inhibit PD. DRV_ENABLE requires system rail/reference health.

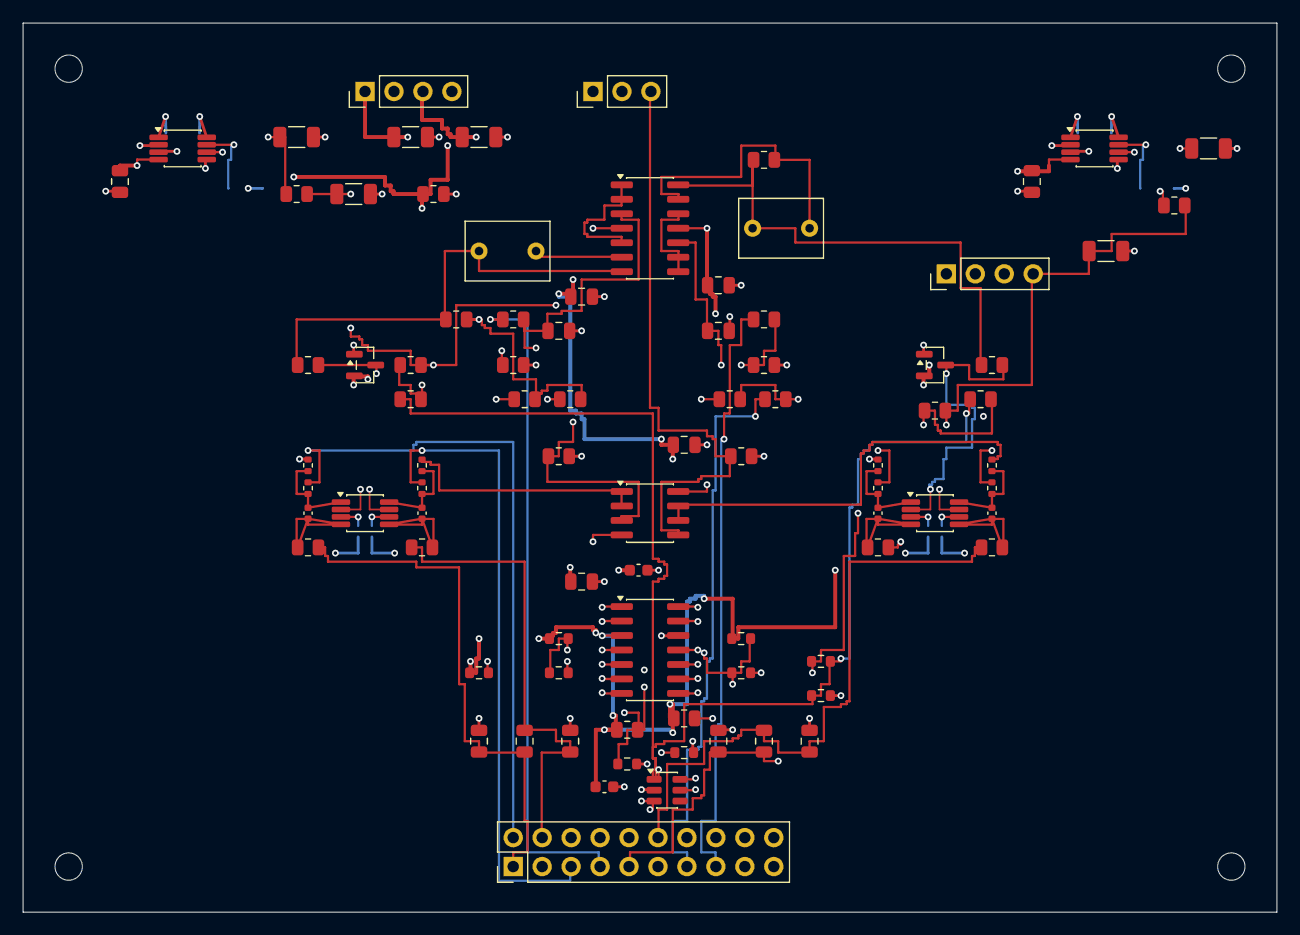
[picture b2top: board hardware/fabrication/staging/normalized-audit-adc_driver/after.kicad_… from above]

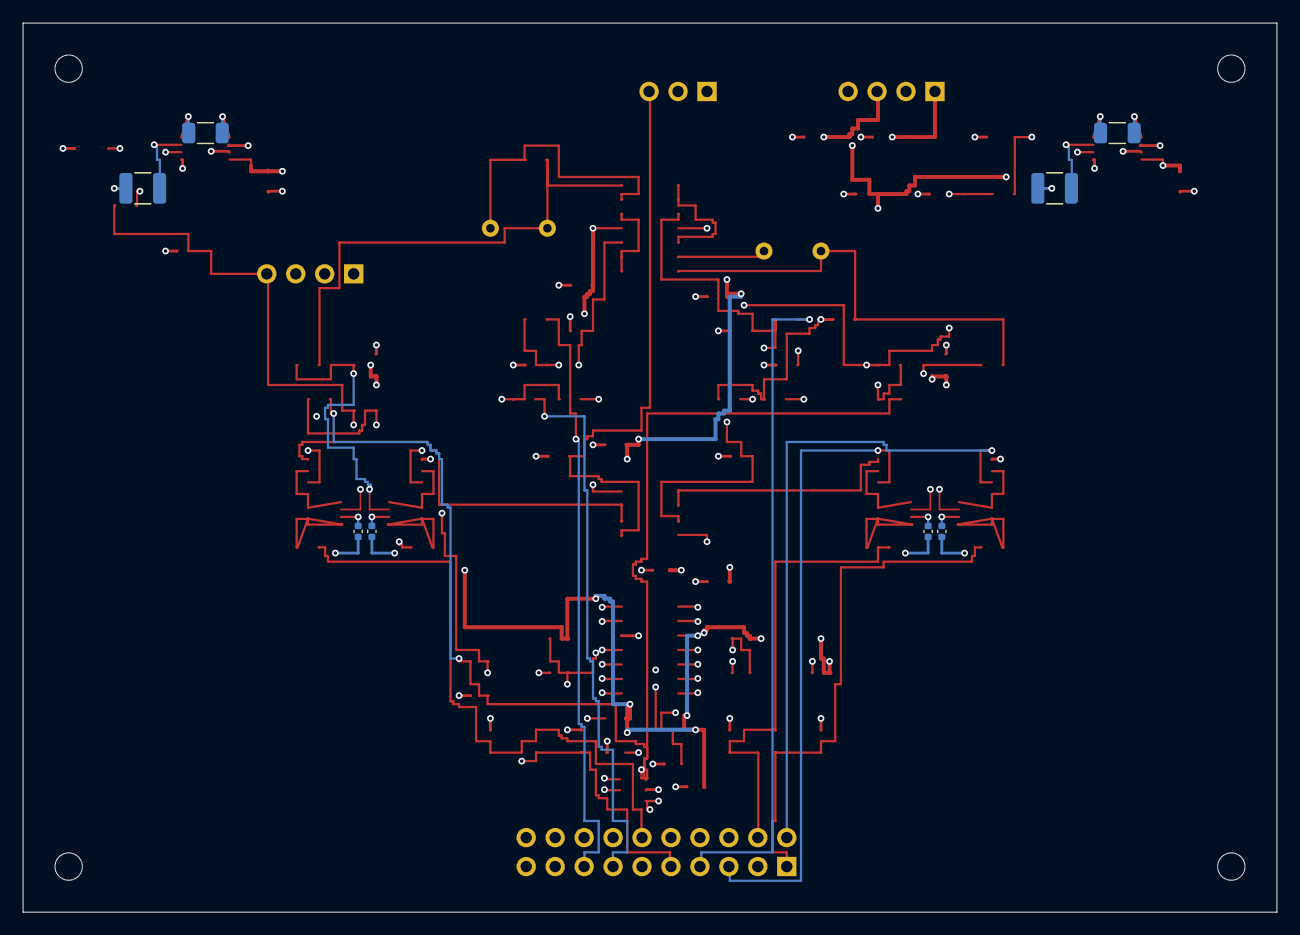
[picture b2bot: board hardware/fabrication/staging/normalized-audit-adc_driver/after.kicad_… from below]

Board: 6 copper layers, 110.0 x 78.0 mm, 98 parts (8 on the bottom side), 55 nets.

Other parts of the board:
H1, H2, H3, H4: M2_CLEARANCE; M2_Clearance

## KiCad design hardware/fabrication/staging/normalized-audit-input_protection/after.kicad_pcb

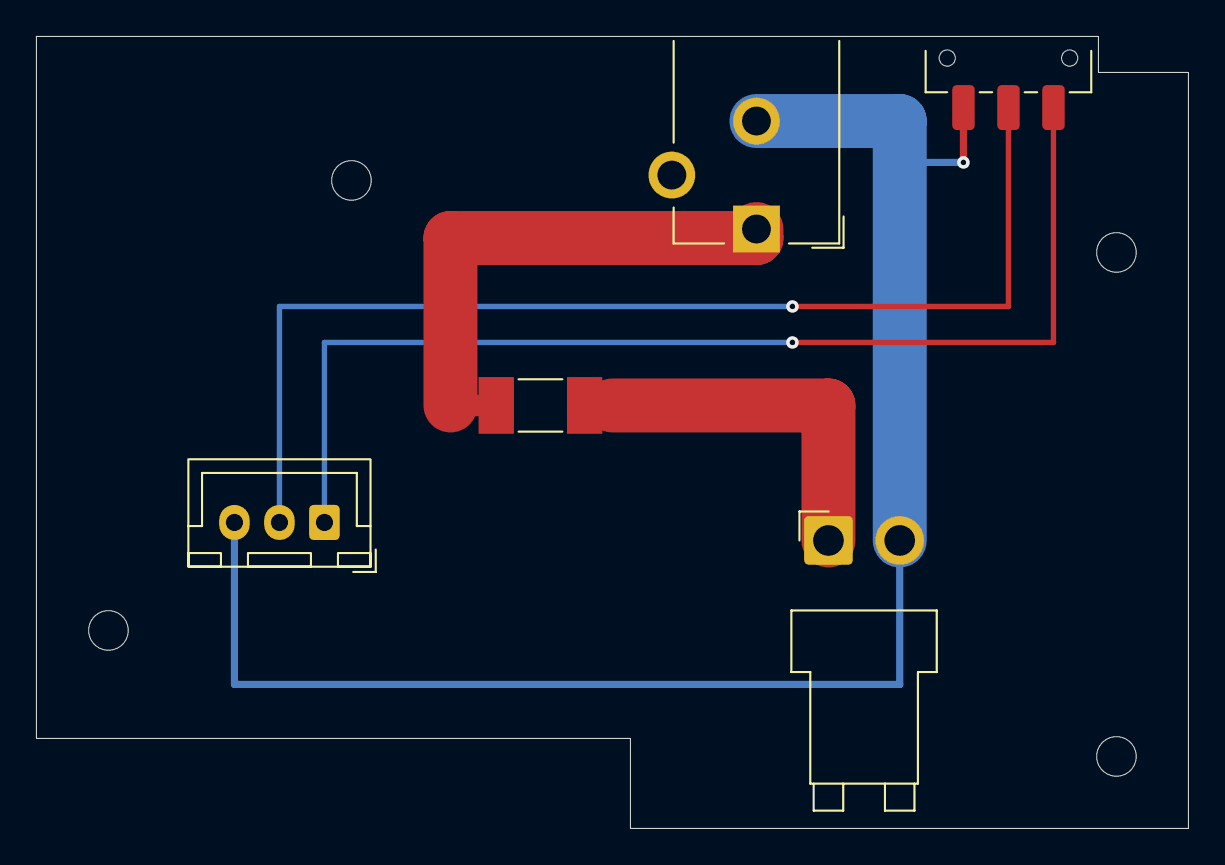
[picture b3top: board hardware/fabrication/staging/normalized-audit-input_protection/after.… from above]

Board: 2 copper layers, 64.0 x 44.0 mm, 9 parts (0 on the bottom side), 5 nets.

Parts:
F1: 0451006.MRL 6A 125V; Fuse_Littelfuse-NANO2-451_453
H1, H2, H3, H4: M2_CLEARANCE; MountingHole_2.2mm_M2
J1: PJ-102AH; PJ102AH_RearEdge_E23
J2: B2PS-VH(LF)(SN); JST_VH_B2PS-VH_1x02_P3.96mm_Horizontal
J3: B3B-XH-A(LF)(SN); JST_XH_B3B-XH-A_1x03_P2.50mm_Vertical
S1: JS102011SAQN; JS102011SAQN_RearEdge_E23

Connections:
/AGND: J1.2, J2.2, J3.3, S1.3
/DC_IN: F1.2, J2.1
/DC_JACK: F1.1, J1.1
/POWER_RUN: J3.2, S1.2
/SWITCH_SUPPLY: J3.1, S1.1

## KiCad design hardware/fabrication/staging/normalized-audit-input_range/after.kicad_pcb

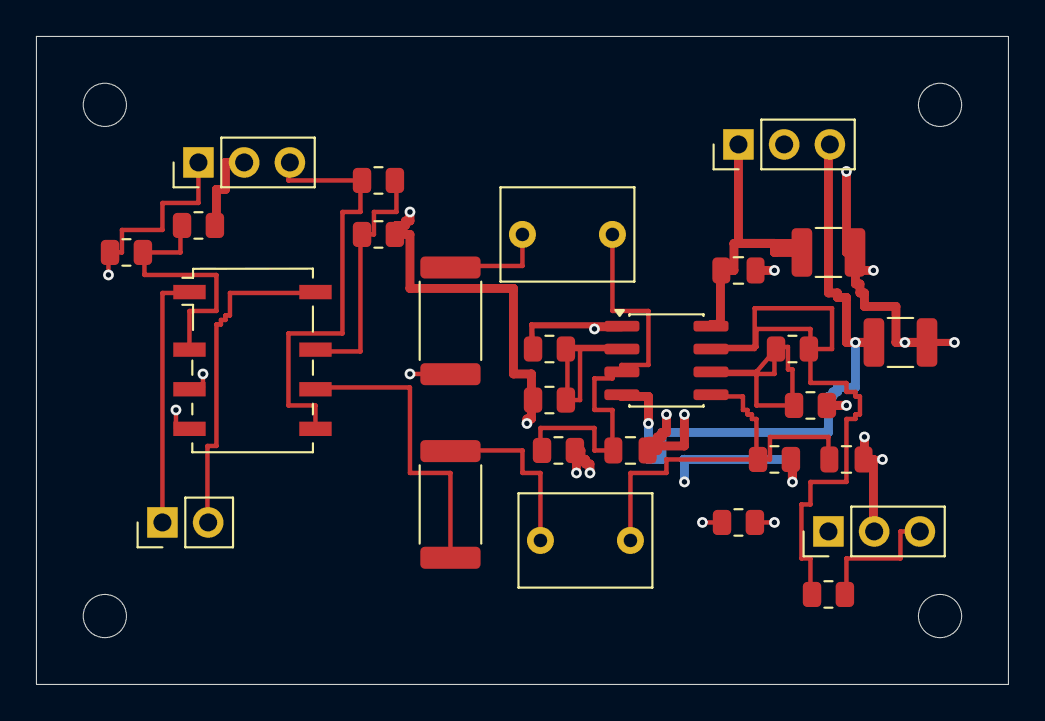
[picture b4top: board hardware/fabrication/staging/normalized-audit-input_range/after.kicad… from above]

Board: 6 copper layers, 54.0 x 36.0 mm, 32 parts (1 on the bottom side), 21 nets.

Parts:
C1, C3: 1uF film 63V 10%; C_Rect_L7.2mm_W5.0mm_P5.00mm
C2, C4: 47pF 50V C0G 5%; C_0805_2012Metric
C5, C6: 100nF 50V X7R; C_0805_2012Metric
C7, C8: 10uF 50V X7R 10%; C_1210_3225Metric
H1, H2, H3, H4: M2_CLEARANCE; M2_Clearance
J1, J2, J3: Conn_01x03; PinHeader_1x03_P2.54mm_Vertical
J4: Conn_01x02; PinHeader_1x02_P2.54mm_Vertical
K1: G6K-2F-Y DC5; Relay_DPDT_Omron_G6K-2F-Y
R1, R8: 33.2k 0.1%; R_0805_2012Metric
R2, R9: 13.7k 0.1%; R_0805_2012Metric
R3, R10: 4.99k 0.1% 1W; R_2512_6332Metric
R4, R11: 68k 0.1%; R_0805_2012Metric
R5, R12: 365 0.1%; R_0805_2012Metric
R6, R13: 1k 0.1%; R_0805_2012Metric
R7, R14: 33.2 0.1%; R_0805_2012Metric
U1: OPA1656ID; SOIC-8_3.9x4.9mm_P1.27mm

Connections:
/5V: J4.1, K1.1
/AGND: C2.2, C4.2, C5.2, C6.2, C7.2, C8.2, J1.2, J2.2, J3.2, R2.2, R4.2, R6.2, R9.2, R11.2, R13.2
/ATTN_L: K1.2, R1.2, R2.1
/ATTN_R: K1.7, R8.2, R9.1
/BUF_IN_L: C1.2, C2.1, R4.1, U1.3
/BUF_IN_R: C3.2, C4.1, R11.1, U1.5
/BUF_OUT_L: R5.2, R7.1, U1.1
/BUF_OUT_R: R12.2, R14.1, U1.7
/GAIN_FB_L: R5.1, R6.1, U1.2
/GAIN_FB_R: R12.1, R13.1, U1.6
/GAIN_LOW: J4.2, K1.8
/HP_SRC_L: C1.1, R3.2
/HP_SRC_R: C3.1, R10.2
/N12: C6.1, C8.1, J3.3, U1.4
/P12: C5.1, C7.1, J3.1, U1.8
/PRE_OUT_L: J2.1, R7.2
/PRE_OUT_R: J2.3, R14.2
/PROC_IN_L: J1.1, K1.4, R1.1
/PROC_IN_R: J1.3, K1.5, R8.1
/RANGE_L: K1.3, R3.1
/RANGE_R: K1.6, R10.1
